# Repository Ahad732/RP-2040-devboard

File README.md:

# Rp2040 Devboard
I have made a devboard with RP 2040. It has 16 mb storage and its just like a raspberry pi pico but in my design. I had build it off a guide from macondo.I built it to learn hardware. This was my first hardware project for hackclub

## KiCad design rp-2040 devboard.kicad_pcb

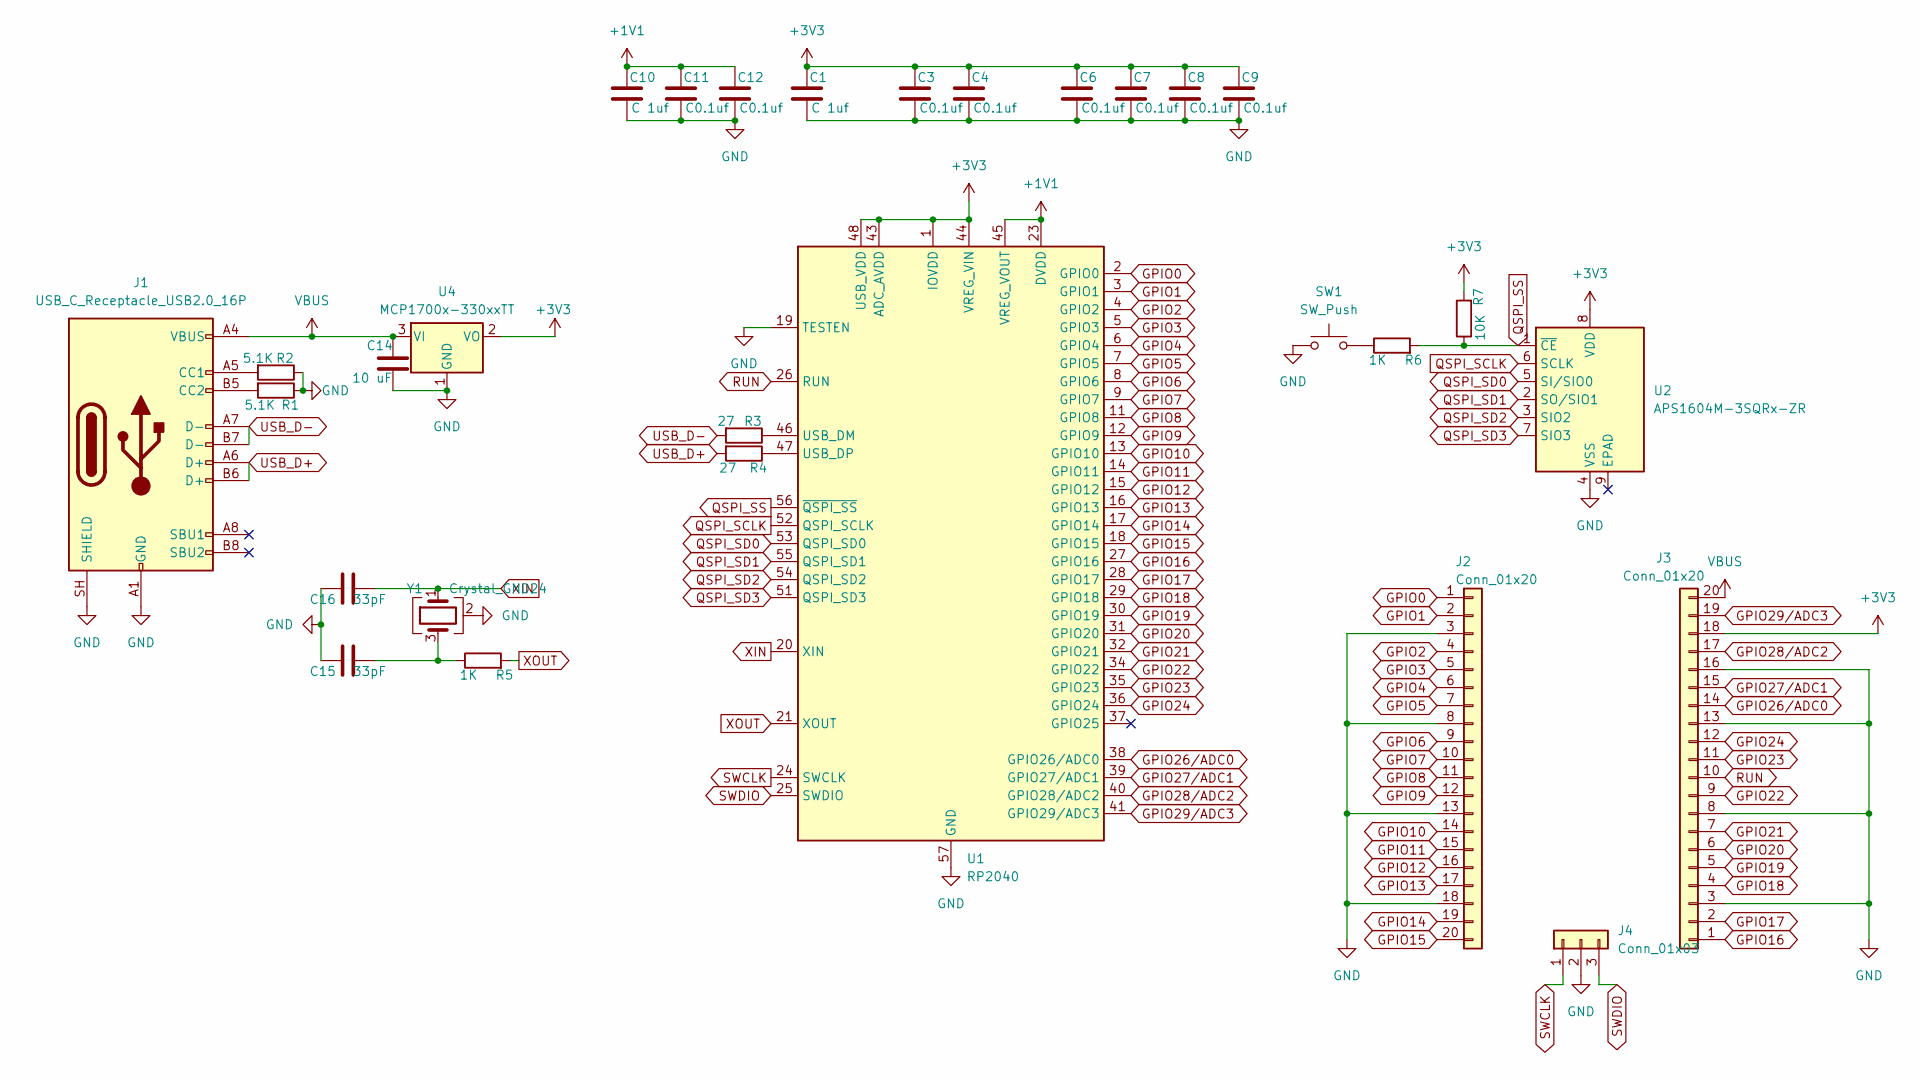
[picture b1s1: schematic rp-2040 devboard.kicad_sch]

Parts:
C1, C10: C 1uf; C_0402_1005Metric
C3, C4, C6, C7, C8, C9, C11, C12: C0.1uf; C_0402_1005Metric
C14: 10 uF; C_0603_1608Metric
C15, C16: 33pF; C_0402_1005Metric
J1: USB_C_Receptacle_USB2.0_16P; USB_C_Receptacle_XKB_U262-16XN-4BVC11
J2, J3: Conn_01x20; PinHeader_1x20_P2.54mm_Vertical
J4: Conn_01x03; PinHeader_1x03_P2.54mm_Vertical
R1, R2: 5.1K; R_0402_1005Metric
R3, R4: 27; R_0402_1005Metric
R5, R6: 1K; R_0402_1005Metric
R7: 10K; R_0402_1005Metric
SW1: SW_Push; SW_Push_SPST_NO_Alps_SKRK
U1: RP2040; QFN-56-1EP_7x7mm_P0.4mm_EP3.2x3.2mm
U2: APS1604M-3SQRx-ZR; Winbond_USON-8-1EP_3x2mm_P0.5mm_EP0.2x1.6mm
U4: MCP1700x-330xxTT; SOT-23
Y1: Crystal_GND24; Crystal_SMD_3225-4Pin_3.2x2.5mm

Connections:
+1V1: C10.1, C11.1, C12.1, U1.23 (DVDD), U1.45 (VREG_VOUT), U1.50 (DVDD)
+3V3: C1.1, C3.1, C4.1, C6.1, C7.1, C8.1, C9.1, J3.18, R7.2, U1.1 (IOVDD), U1.10 (IOVDD), U1.22 (IOVDD), U1.33 (IOVDD), U1.42 (IOVDD), U1.43 (ADC_AVDD), U1.44 (VREG_VIN), U1.48 (USB_VDD), U1.49 (IOVDD), U2.8 (VDD), U4.2 (VO); also elsewhere on the board
GND: C1.2, C3.2, C4.2, C6.2, C7.2, C8.2, C9.2, C10.2, C11.2, C12.2, C14.2, C15.1, C16.1, J1.A1 (GND), J1.A12 (GND), J1.B1 (GND), J1.B12 (GND), J1.SH (SHIELD), J2.3, J2.8, J2.13, J2.18, J3.3, J3.8, J3.13, J3.16, J4.2, R1.1, R2.1, SW1.1, U1.19 (TESTEN), U1.57 (GND), U2.4 (VSS), U4.1 (GND), Y1.2 (G), Y1.4 (G); also elsewhere on the board
GPIO0: J2.1, U1.2 (GPIO0)
GPIO1: J2.2, U1.3 (GPIO1)
GPIO2: J2.4, U1.4 (GPIO2)
GPIO3: J2.5, U1.5 (GPIO3)
GPIO4: J2.6, U1.6 (GPIO4)
GPIO5: J2.7, U1.7 (GPIO5)
GPIO6: J2.9, U1.8 (GPIO6)
GPIO7: J2.10, U1.9 (GPIO7)
GPIO8: J2.11, U1.11 (GPIO8)
GPIO9: J2.12, U1.12 (GPIO9)
GPIO10: J2.14, U1.13 (GPIO10)
GPIO11: J2.15, U1.14 (GPIO11)
GPIO12: J2.16, U1.15 (GPIO12)
GPIO13: J2.17, U1.16 (GPIO13)
GPIO14: J2.19, U1.17 (GPIO14)
GPIO15: J2.20, U1.18 (GPIO15)
GPIO16: J3.1, U1.27 (GPIO16)
GPIO17: J3.2, U1.28 (GPIO17)
GPIO18: J3.4, U1.29 (GPIO18)
GPIO19: J3.5, U1.30 (GPIO19)
GPIO20: J3.6, U1.31 (GPIO20)
GPIO21: J3.7, U1.32 (GPIO21)
GPIO22: J3.9, U1.34 (GPIO22)
GPIO23: J3.11, U1.35 (GPIO23)
GPIO24: J3.12, U1.36 (GPIO24)
GPIO26/ADC0: J3.14, U1.38 (GPIO26/ADC0)
GPIO27/ADC1: J3.15, U1.39 (GPIO27/ADC1)
GPIO28/ADC2: J3.17, U1.40 (GPIO28/ADC2)
GPIO29/ADC3: J3.19, U1.41 (GPIO29/ADC3)
unnamed: C15.2, R5.1, Y1.3
unnamed: J1.A5 (CC1), R2.2
unnamed: J1.B5 (CC2), R1.2
unnamed: R6.1, SW1.2
unnamed: R3.1, U1.46 (USB_DM)
unnamed: R4.1, U1.47 (USB_DP)
QSPI_SCLK: U1.52 (QSPI_SCLK), U2.6 (SCLK)
QSPI_SD0: U1.53 (QSPI_SD0), U2.5 (SI/SIO0)
QSPI_SD1: U1.55 (QSPI_SD1), U2.2 (SO/SIO1)
QSPI_SD2: U1.54 (QSPI_SD2), U2.3 (SIO2)
QSPI_SD3: U1.51 (QSPI_SD3), U2.7 (SIO3)
QSPI_SS: R6.2, R7.1, U1.56 (~QSPI_SS), U2.1 (~CE)
RUN: J3.10, U1.26 (RUN)
SWCLK: J4.1, U1.24 (SWCLK)
SWDIO: J4.3, U1.25 (SWDIO)
USB_D+: J1.A6 (D+), J1.B6 (D+), R4.2
USB_D-: J1.A7 (D-), J1.B7 (D-), R3.2
VBUS: C14.1, J1.A4 (VBUS), J1.A9 (VBUS), J1.B4 (VBUS), J1.B9 (VBUS), J3.20, U4.3 (VI)
XIN: C16.2, U1.20 (XIN), Y1.1
XOUT: R5.2, U1.21 (XOUT)

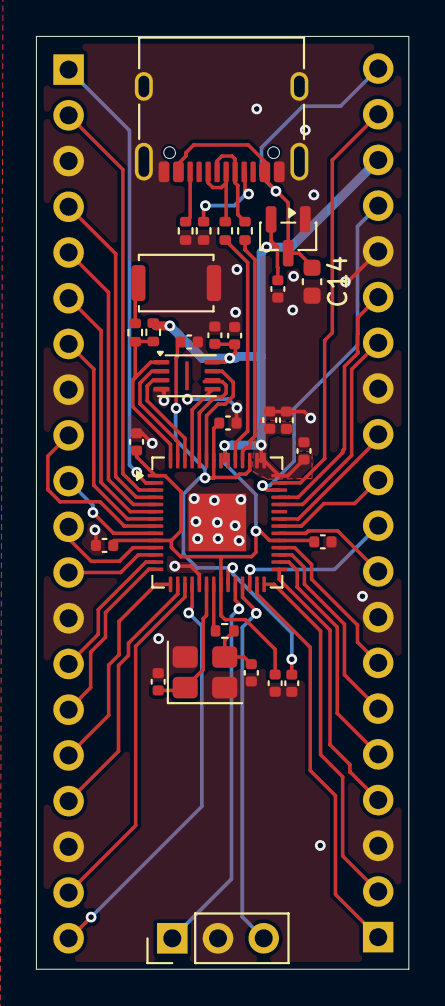
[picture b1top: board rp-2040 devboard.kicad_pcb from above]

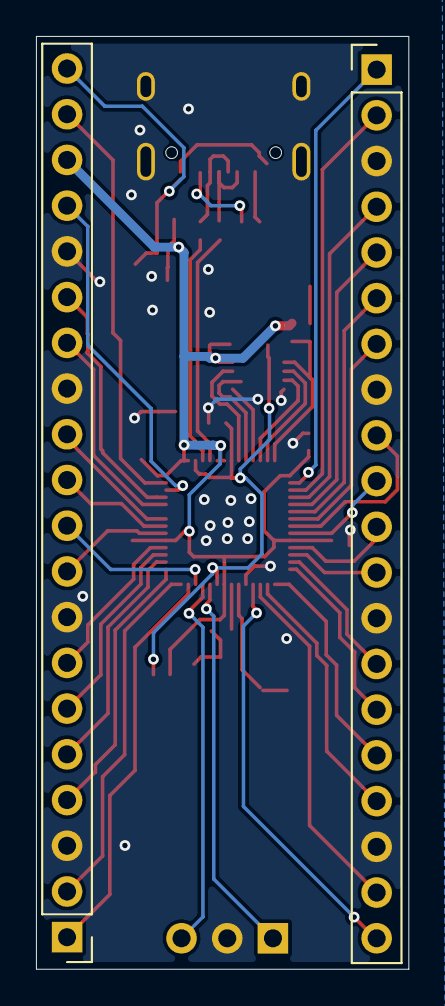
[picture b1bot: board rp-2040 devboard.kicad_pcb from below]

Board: 2 copper layers, 20.7 x 51.8 mm, 32 parts (2 on the bottom side), 52 nets.

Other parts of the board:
C1#2: C 1uf; C_0402_1005Metric
C5, C9#2: C0.1uf; C_0402_1005Metric

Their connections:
+3V3: C1#2.1, C5.1, C9#2.1; also elsewhere on the board
GND: C1#2.2, C5.2, C9#2.2; also elsewhere on the board

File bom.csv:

Designator,Value,Quantity,Amount,Link
PCB,,5,2.1,http://jlcpcb.com/
"C1_2, C1, C10",C 1uf,50,0.24,https://www.lcsc.com/product-detail/C2929192.html
"C11, C12, C3, C4, C5, C6, C7, C8, C9_2, C9",C0.1uf,10,0.03,https://www.lcsc.com/product-detail/C237172.html
C14,10 uF,50,0.76,https://www.lcsc.com/product-detail/C105490.html
"C15, C16",33pF,100,0.14,https://www.lcsc.com/product-detail/C482484.html
J1,USB_C_Receptacle_USB2.0_16P,10,0.67,https://www.lcsc.com/product-detail/C393939.html
"J2, J3",Conn_01x20,0,0,dnp
J4,Conn_01x03,0,0,dnp
"R1, R2",5.1K,100,0.23,https://www.lcsc.com/product-detail/C2907044.html
"R3, R4",27,100,0.24,https://www.lcsc.com/product-detail/C137753.html
"R5, R6",1K,100,0.31,https://www.lcsc.com/product-detail/C2907002.html
R7,10K,100,0.14,https://www.lcsc.com/product-detail/C60490.html
SW1,SW_Push,1,0.59,https://www.lcsc.com/product-detail/C221896.html
U1,RP2040,1,0.99,https://www.lcsc.com/product-detail/C2040.html
U2,APS1604M-3SQRx-ZR,1,2.31,https://www.lcsc.com/product-detail/C22423595.html
U4,MCP1700x-330xxTT,5,0.41,https://www.lcsc.com/product-detail/C41381676.html
Y1,Crystal_GND24,5,0.51,https://www.lcsc.com/product-detail/C9002.html
,,PCB Shipping cost,7.65,
,,LCSC Shipping cost,8,
,,Total,25.32,

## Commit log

2026-06-25 made the devboard
2026-06-25 wrote the readme
2026-06-25 added images, CAD and gerber files
2026-06-26 everything done
2026-06-26 removed history files
2026-06-26 submitting
